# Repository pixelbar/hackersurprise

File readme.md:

# Hacker Suprise Assembly Instructions

Congratulations, you have a Hacker Suprise. This document will guide you through the assembly of your suprise.

## Step 0:
EAT THE CHOCOLATE NOW, otherwise you have to wait until you have washed your hands. Soldering involves working with lead and that does not mix well with food.

## Step 1:
Check if you have all the required parts:
1. Pcb
2. SMD Resistors 2x (in white tape)
3. SMD LED (Colors can vary)
4. Through hole resistor
5. RGB flashing LED (shape can vary)
6. 2x2 female header
7. 2x2 male header

If you are missing parts, please tell the person you got the suprise from. Spare parts are available.

## Step 2
Apply tiny blobs of solder on the top pads of the board, on the side where you hold your soldering iron.

## Step 3
Using tweezers, solder one side of the SMD resistor (the black components in the paper tape). When they are fixed, solder the other side.

## Step 4
Apply the same method as step 2 to one side of the larger pads

## Step 5
The LEDs are directional. There is an arrow on the bottom and a green dot on the top of the component, this should point downward towards the white line under the pads. Solder one side and then the other.

## Step 6
Put the through hole resistor in the board and solder it.

## Step 7
Put the LED in the board (pay attention to the footprint on the board and the straight edge on the LED) and solder it.

## Step 8
Solder the male headers to the rear of the board. This will be easier if you insert the headers in a breadboard. Solder one pad, make sure the board is level and then solder the other pads.

## Step 9
Solder the female headers to your badge, such that you can insert your addon to the front.

## Step 10
Insert the addon with the board pointing to the top of the badge.

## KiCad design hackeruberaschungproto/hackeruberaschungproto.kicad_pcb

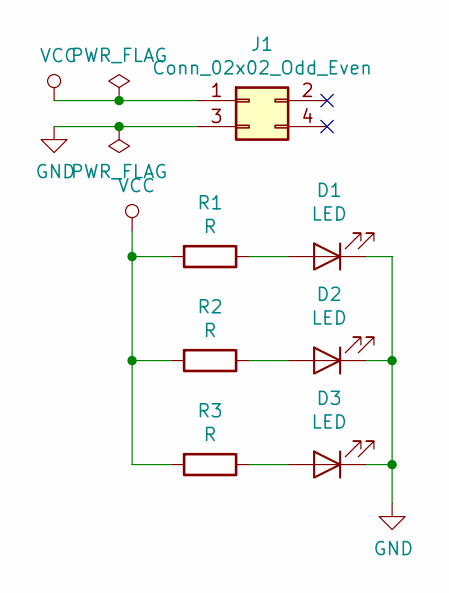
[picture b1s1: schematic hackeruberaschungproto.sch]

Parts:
D1: LED; LED_D5.0mm_Clear
D2, D3: LED; LED_1206_3216Metric
J1: Conn_02x02_Odd_Even; PinHeader_2x02_P2.54mm_Horizontal
R1: R; R_Axial_DIN0207_L6.3mm_D2.5mm_P7.62mm_Horizontal
R2, R3: R; R_0805_2012Metric

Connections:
GND: D1.1 (K), D2.1 (K), D3.1 (K), J1.3
unnamed: D1.2 (A), R1.1
unnamed: D2.2 (A), R2.1
unnamed: D3.2 (A), R3.1
VCC: J1.1, R1.2, R2.2, R3.2

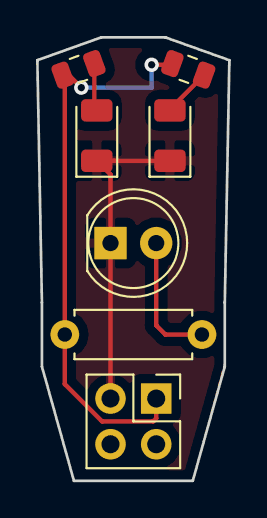
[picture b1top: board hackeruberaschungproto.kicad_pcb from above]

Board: 2 copper layers, 10.7 x 24.6 mm, 7 parts (0 on the bottom side), 5 nets.
